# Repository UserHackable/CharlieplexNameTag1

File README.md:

## CharlieplexNameTag 

### Board dimensions

* (393701, 196850) original units
* (3.9370, 1.9685) inches
* (100.0001, 49.9999) mm

| Front | Back |
| --- | --- |
|  |  |

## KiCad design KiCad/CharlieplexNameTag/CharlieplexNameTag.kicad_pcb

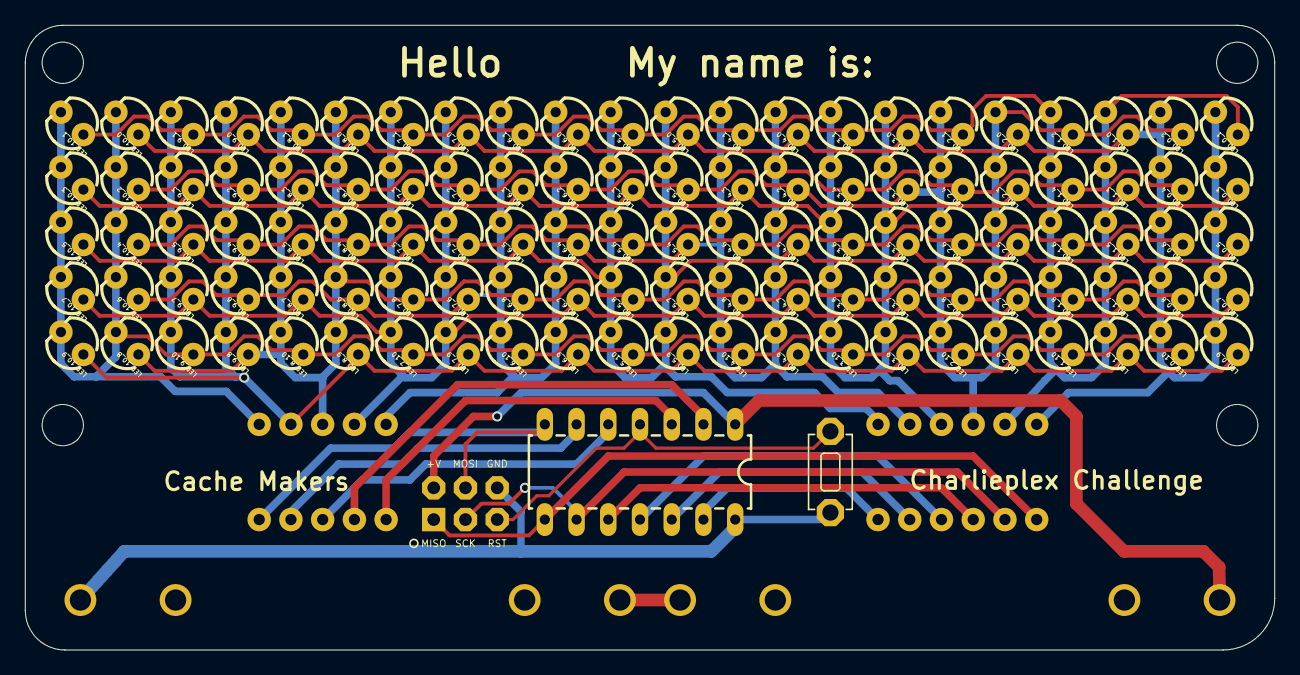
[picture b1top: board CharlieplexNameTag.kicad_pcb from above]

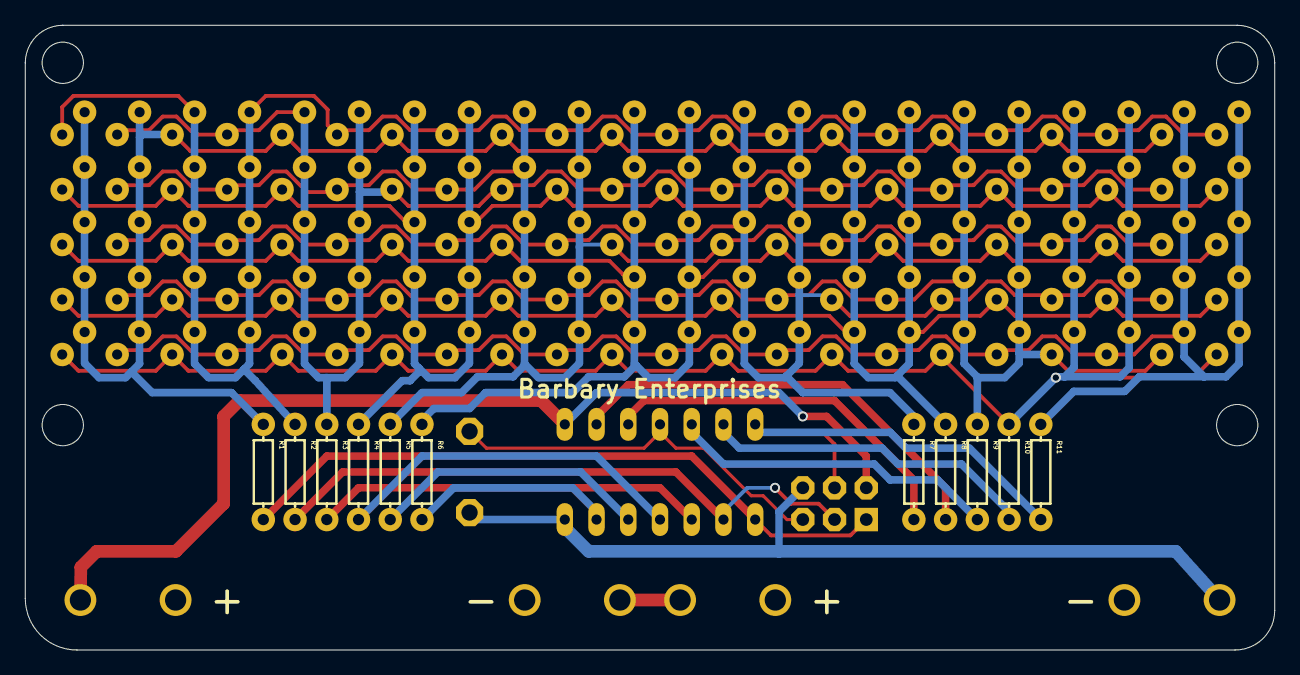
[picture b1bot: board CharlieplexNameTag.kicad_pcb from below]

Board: 2 copper layers, 100.0 x 50.0 mm, 130 parts (13 on the bottom side), 26 nets.

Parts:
BAT1, BAT2: BATTERY-AAA
J1: AVR_SPI_PRG_6LABELED; 2X3-NS
LED_0_1, LED_0_2, LED_0_3, LED_0_4, LED_0_5, LED_0_6, LED_0_7, LED_0_8, LED_0_9, LED_0_10, LED_1_0, LED_1_2, LED_1_3, LED_1_4, LED_1_5, LED_1_6, LED_1_7, LED_1_8, LED_1_9, LED_1_10, LED_2_0, LED_2_1, LED_2_3, LED_2_4, LED_2_5, LED_2_6, LED_2_7, LED_2_8, LED_2_9, LED_2_10, LED_3_0, LED_3_1, LED_3_2, LED_3_4, LED_3_5, LED_3_6, LED_3_7, LED_3_8, LED_3_9, LED_3_10, LED_4_0, LED_4_1, LED_4_2, LED_4_3, LED_4_5, LED_4_6, LED_4_7, LED_4_8, LED_4_9, LED_4_10, LED_5_0, LED_5_1, LED_5_2, LED_5_3, LED_5_4, LED_5_6, LED_5_7, LED_5_8, LED_5_9, LED_5_10, LED_6_0, LED_6_1, LED_6_2, LED_6_3, LED_6_4, LED_6_5, LED_6_7, LED_6_8, LED_6_9, LED_6_10, LED_7_0, LED_7_1, LED_7_2, LED_7_3, LED_7_4, LED_7_5, LED_7_6, LED_7_8, LED_7_9, LED_7_10, LED_8_0, LED_8_1, LED_8_2, LED_8_3, LED_8_4, LED_8_5, LED_8_6, LED_8_7, LED_8_9, LED_8_10, LED_9_0, LED_9_1, LED_9_2, LED_9_3, LED_9_4, LED_9_5, LED_9_6, LED_9_7, LED_9_8, LED_9_10, LED_10_0, LED_10_1, LED_10_2, LED_10_3, LED_10_4, LED_10_5, LED_10_6, LED_10_7, LED_10_8, LED_10_9: LED3MM
R1, R2, R3, R4, R5, R6, R7, R8, R9, R10, R11: AXIAL-0.3
STANDOFF1, STANDOFF2, STANDOFF3, STANDOFF4: STAND-OFF
U$1: ATTINY84ATTINY84-20PU; DIL14
U$2: TAC_SPST_NO

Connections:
5V: BAT1.PWR@1, J1.2, U$1.1
D0: R6.P$2, U$1.13
D1: R5.P$2, U$1.12
D2: R4.P$2, U$1.11
D3: R3.P$2, U$1.10
D4: J1.3, R2.P$2, U$1.9
D5: J1.1, R1.P$2, U$1.8
D6: J1.4, R11.P$2, U$1.7
D7: R10.P$2, U$1.6
D8: R8.P$2, U$1.2
D9: R7.P$2, U$1.3
D10: R9.P$2, U$1.5
GND: BAT2.GND@1, J1.6, U$1.14, U$2.P$1
unnamed: BAT1.GND@1, BAT2.PWR@1
P0: LED_0_1.K, LED_0_2.K, LED_0_3.K, LED_0_4.K, LED_0_5.K, LED_0_6.K, LED_0_7.K, LED_0_8.K, LED_0_9.K, LED_0_10.K, LED_1_0.A, LED_2_0.A, LED_3_0.A, LED_4_0.A, LED_5_0.A, LED_6_0.A, LED_7_0.A, LED_8_0.A, LED_9_0.A, LED_10_0.A, R1.P$1
P1: LED_0_1.A, LED_1_0.K, LED_1_2.K, LED_1_3.K, LED_1_4.K, LED_1_5.K, LED_1_6.K, LED_1_7.K, LED_1_8.K, LED_1_9.K, LED_1_10.K, LED_2_1.A, LED_3_1.A, LED_4_1.A, LED_5_1.A, LED_6_1.A, LED_7_1.A, LED_8_1.A, LED_9_1.A, LED_10_1.A, R2.P$1
P2: LED_0_2.A, LED_1_2.A, LED_2_0.K, LED_2_1.K, LED_2_3.K, LED_2_4.K, LED_2_5.K, LED_2_6.K, LED_2_7.K, LED_2_8.K, LED_2_9.K, LED_2_10.K, LED_3_2.A, LED_4_2.A, LED_5_2.A, LED_6_2.A, LED_7_2.A, LED_8_2.A, LED_9_2.A, LED_10_2.A, R3.P$1
P3: LED_0_3.A, LED_1_3.A, LED_2_3.A, LED_3_0.K, LED_3_1.K, LED_3_2.K, LED_3_4.K, LED_3_5.K, LED_3_6.K, LED_3_7.K, LED_3_8.K, LED_3_9.K, LED_3_10.K, LED_4_3.A, LED_5_3.A, LED_6_3.A, LED_7_3.A, LED_8_3.A, LED_9_3.A, LED_10_3.A, R4.P$1
P4: LED_0_4.A, LED_1_4.A, LED_2_4.A, LED_3_4.A, LED_4_0.K, LED_4_1.K, LED_4_2.K, LED_4_3.K, LED_4_5.K, LED_4_6.K, LED_4_7.K, LED_4_8.K, LED_4_9.K, LED_4_10.K, LED_5_4.A, LED_6_4.A, LED_7_4.A, LED_8_4.A, LED_9_4.A, LED_10_4.A, R5.P$1
P5: LED_0_5.A, LED_1_5.A, LED_2_5.A, LED_3_5.A, LED_4_5.A, LED_5_0.K, LED_5_1.K, LED_5_2.K, LED_5_3.K, LED_5_4.K, LED_5_6.K, LED_5_7.K, LED_5_8.K, LED_5_9.K, LED_5_10.K, LED_6_5.A, LED_7_5.A, LED_8_5.A, LED_9_5.A, LED_10_5.A, R6.P$1
P6: LED_0_6.A, LED_1_6.A, LED_2_6.A, LED_3_6.A, LED_4_6.A, LED_5_6.A, LED_6_0.K, LED_6_1.K, LED_6_2.K, LED_6_3.K, LED_6_4.K, LED_6_5.K, LED_6_7.K, LED_6_8.K, LED_6_9.K, LED_6_10.K, LED_7_6.A, LED_8_6.A, LED_9_6.A, LED_10_6.A, R7.P$1
P7: LED_0_7.A, LED_1_7.A, LED_2_7.A, LED_3_7.A, LED_4_7.A, LED_5_7.A, LED_6_7.A, LED_7_0.K, LED_7_1.K, LED_7_2.K, LED_7_3.K, LED_7_4.K, LED_7_5.K, LED_7_6.K, LED_7_8.K, LED_7_9.K, LED_7_10.K, LED_8_7.A, LED_9_7.A, LED_10_7.A, R8.P$1
P8: LED_0_8.A, LED_1_8.A, LED_2_8.A, LED_3_8.A, LED_4_8.A, LED_5_8.A, LED_6_8.A, LED_7_8.A, LED_8_0.K, LED_8_1.K, LED_8_2.K, LED_8_3.K, LED_8_4.K, LED_8_5.K, LED_8_6.K, LED_8_7.K, LED_8_9.K, LED_8_10.K, LED_9_8.A, LED_10_8.A, R9.P$1
P9: LED_0_9.A, LED_1_9.A, LED_2_9.A, LED_3_9.A, LED_4_9.A, LED_5_9.A, LED_6_9.A, LED_7_9.A, LED_8_9.A, LED_9_0.K, LED_9_1.K, LED_9_2.K, LED_9_3.K, LED_9_4.K, LED_9_5.K, LED_9_6.K, LED_9_7.K, LED_9_8.K, LED_9_10.K, LED_10_9.A, R10.P$1
P10: LED_0_10.A, LED_1_10.A, LED_2_10.A, LED_3_10.A, LED_4_10.A, LED_5_10.A, LED_6_10.A, LED_7_10.A, LED_8_10.A, LED_9_10.A, LED_10_0.K, LED_10_1.K, LED_10_2.K, LED_10_3.K, LED_10_4.K, LED_10_5.K, LED_10_6.K, LED_10_7.K, LED_10_8.K, LED_10_9.K, R11.P$1
RST: J1.5, U$1.4, U$2.P$2

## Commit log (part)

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2016-04-08 from Makefile
